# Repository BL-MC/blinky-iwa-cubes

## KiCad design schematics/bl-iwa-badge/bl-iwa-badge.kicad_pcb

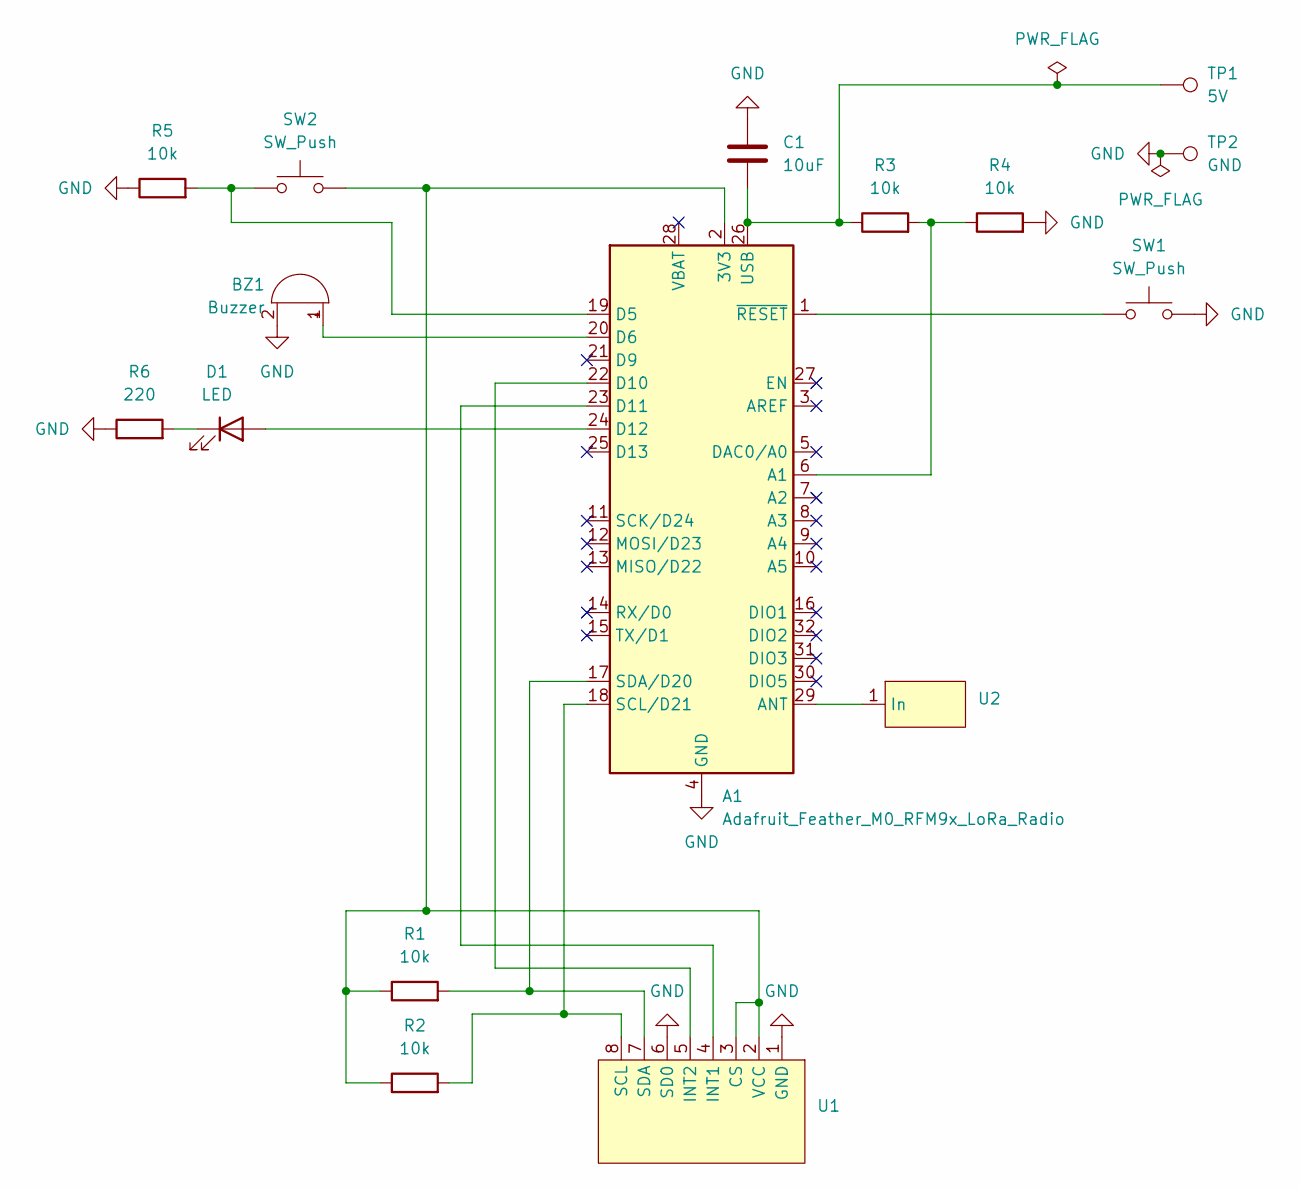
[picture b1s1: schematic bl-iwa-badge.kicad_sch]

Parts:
A1: Adafruit_Feather_M0_RFM9x_LoRa_Radio; Adafruit_Feather_M0_RFM
BZ1: Buzzer; Buzzer_15x7.5RM7.6
C1: 10uF; C_1206_3216Metric_Pad1.33x1.80mm_HandSolder
D1: LED; LED_D5.0mm
R1, R2, R3, R4, R5: 10k; R_1206_3216Metric_Pad1.30x1.75mm_HandSolder
R6: 220; R_1206_3216Metric_Pad1.30x1.75mm_HandSolder
SW1: SW_Push; SW_PUSH_6mm
SW2: SW_Push; bigButton
TP1: 5V; PCB_THT
TP2: GND; PCB_THT
U1: ADXL345_Breakout
U2: SpringAnt33

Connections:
GND: A1.4 (GND), BZ1.2 (-), C1.1, R4.2, R5.1, R6.1, SW1.2, TP2.1, U1.1 (GND), U1.6 (SD0)
unnamed: A1.2 (3V3), R1.1, R2.1, SW2.2, U1.2 (VCC), U1.3 (CS)
unnamed: A1.6 (A1), R3.2, R4.1
unnamed: A1.29 (ANT), U2.1 (In)
unnamed: A1.19 (D5), R5.2, SW2.1
unnamed: A1.20 (D6), BZ1.1 (+)
unnamed: A1.22 (D10), U1.5 (INT2)
unnamed: A1.23 (D11), U1.4 (INT1)
unnamed: A1.24 (D12), D1.2 (A)
unnamed: A1.18 (SCL/D21), R2.2, U1.8 (SCL)
unnamed: A1.17 (SDA/D20), R1.2, U1.7 (SDA)
unnamed: A1.26 (USB), C1.2, R3.1, TP1.1
unnamed: A1.1 (~RESET), SW1.1
unnamed: D1.1 (K), R6.2

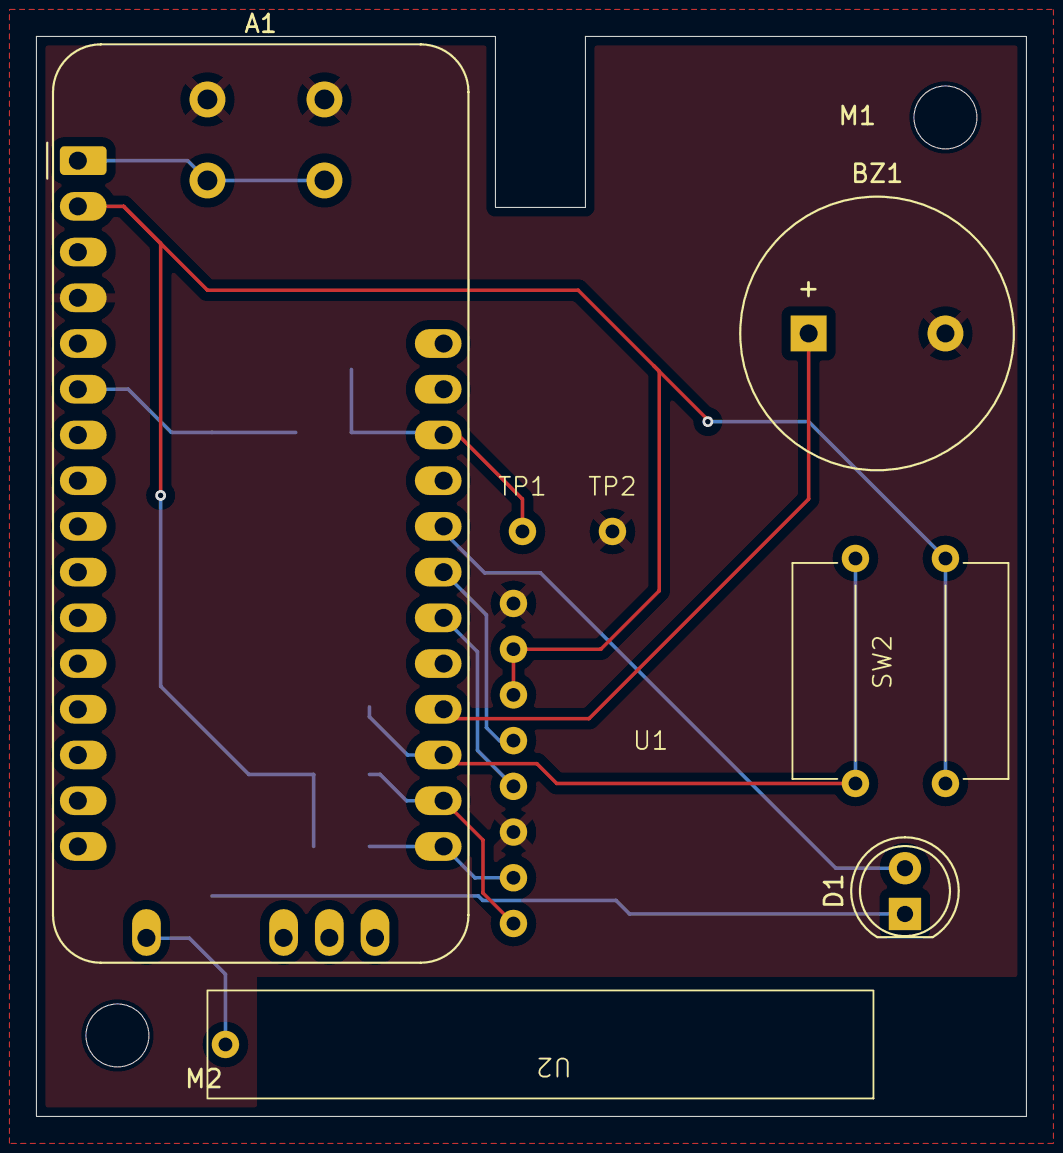
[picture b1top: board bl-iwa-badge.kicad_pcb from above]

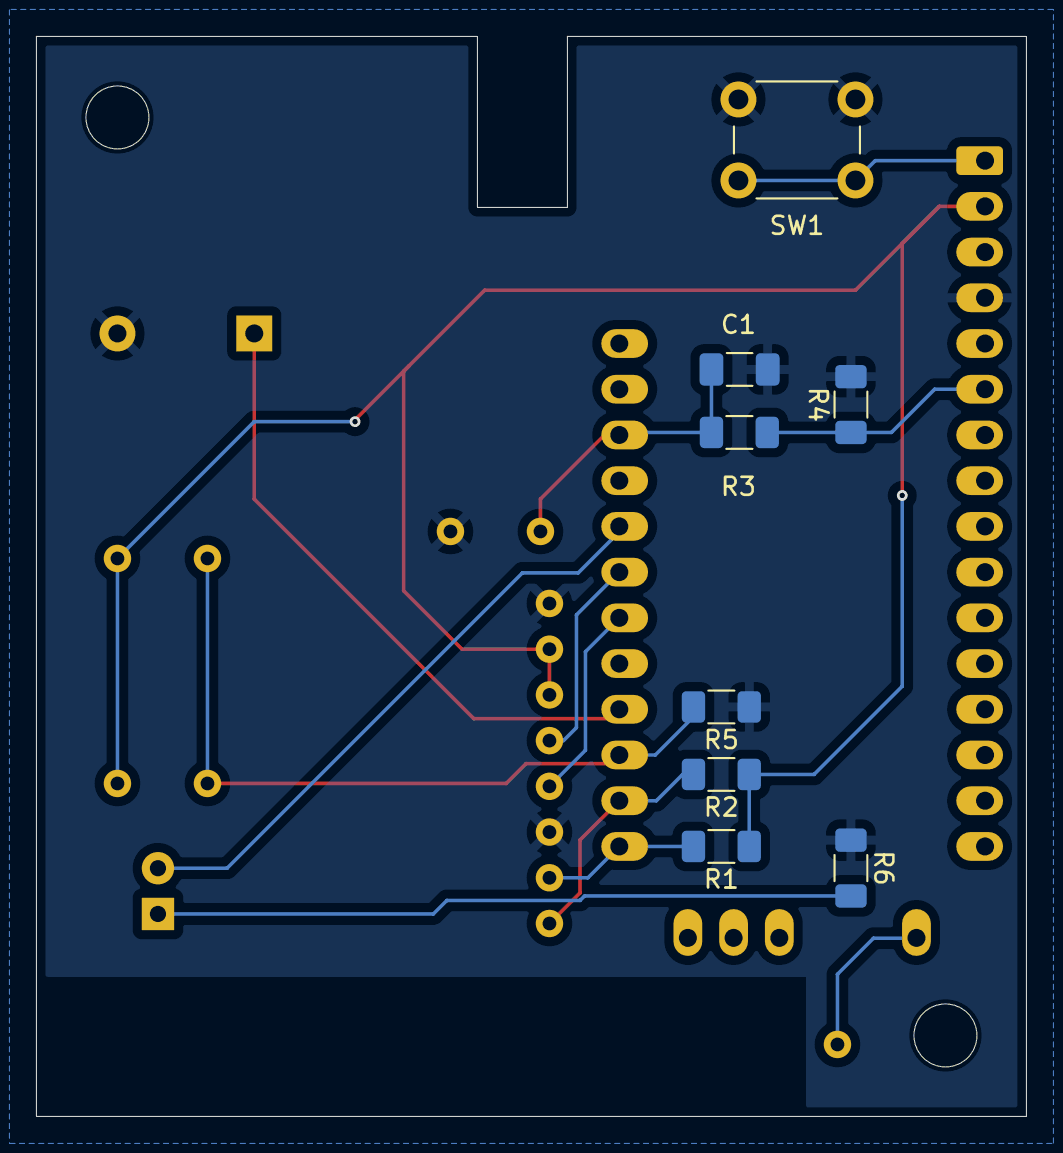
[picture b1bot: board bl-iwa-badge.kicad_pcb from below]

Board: 2 copper layers, 55.0 x 60.0 mm, 18 parts (8 on the bottom side), 14 nets.

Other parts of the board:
M1, M2: MountingHole_3.5mm

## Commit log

2024-06-11 badge speaker workaround
2024-07-14 new pcb
2024-07-14 multiple station commbug fixed
2024-07-14 added continuous move alarm
2024-07-16 working with one press auth
2024-07-18 fixed id bug in auth and warn
2024-07-25 changed structs to unions
2024-08-04 added 4 cubes
2024-08-09 new button long push
2024-08-10 opertional
2024-08-11 changed movement threshold to 4
2024-08-12 added sleep mode
2024-08-12 added raio and watchdog sleep if init on battery
2024-08-12 added blink lite to transmit
2024-09-05 added multiple transmits of badge msgs
2024-09-09 changed bandwidth and fixed up cad
2024-12-08 before checkout of wifi module
2024-12-13 working picoW
2024-12-16 added ifika
2024-12-19 added beep nof not internet
2025-01-14 fixed web page serve header check
